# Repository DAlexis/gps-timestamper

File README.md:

GPS timestamper project
=======================

Open-source device based on STM32 that provides precision time stamps
of trigger signal connected to input. It use GPS PPS signal to provide
~1uS precision time mesurment. Also it makes self-calibration by PPS
every second.

Device may be used to synchronize any signals and data streams without
wired or wireless connection i.e. in geophysical researches, lightning 
detection networks, seismology and others

Currently project in protortype state and under development. Primary
function (precision timestamping) works correctly.

# Build
To build firmware you may have installed `arm-gcc` toolchain on your
linux system. If you do not need unit tests, simply comment out
corresponding line in root CMakeLists.txt (to build tests `gtest` should
be installed on your system)

Run `build.sh` and thats all. To flash MCU, connect ST-Link device to
PC and then run `flash.sh`.

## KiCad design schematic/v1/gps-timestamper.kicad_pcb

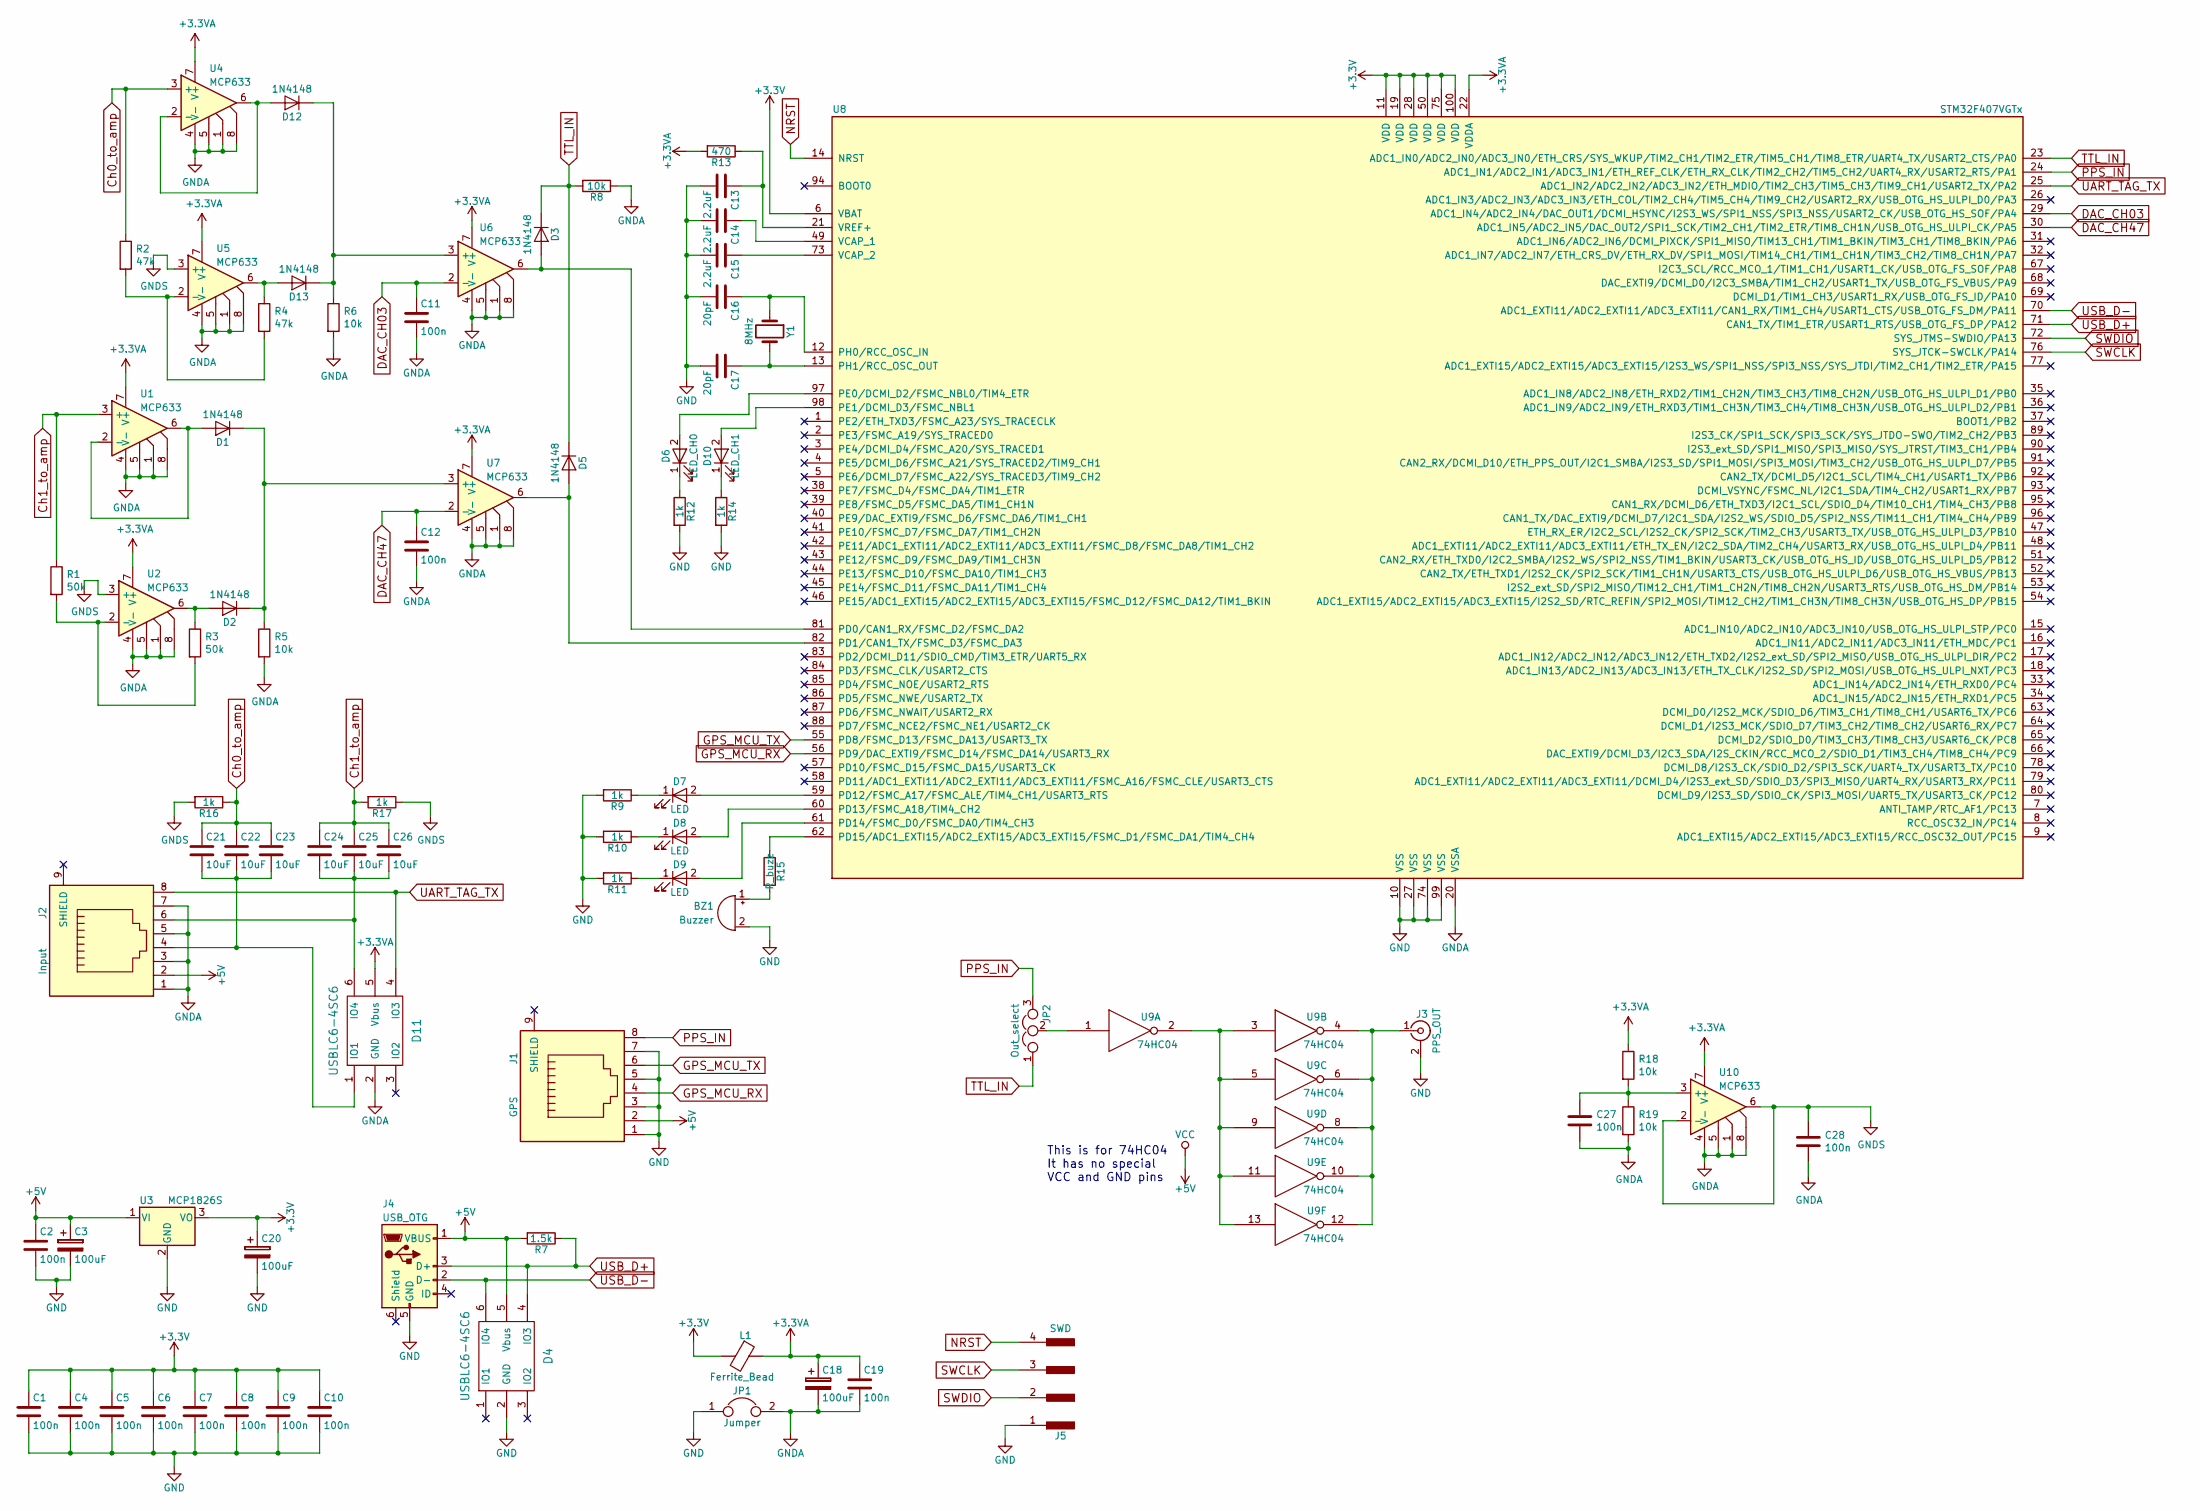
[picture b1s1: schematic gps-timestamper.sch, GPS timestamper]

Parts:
BZ1: Buzzer; Buzzer_12x9.5RM7.6
C1, C2, C4, C5, C6, C7, C8, C9, C10, C11, C12, C19, C27, C28: 100n; C_0805
C3, C18, C20: 100uF; CP_Tantalum_Case-B_EIA-3528-21_Wave
C13, C14, C15: 2.2uF; C_0805
C16, C17: 20pF; C_0805
C21, C22, C23, C24, C25, C26: 10uF; C_0805
D1, D2, D3, D5, D12, D13: 1N4148; D_SOD-323
D4, D11: USBLC6-4SC6; SOT-23-6
D6: LED_CH0; LED_0805
D7, D8, D9: LED; LED_0805
D10: LED_CH1; LED_0805
J1: GPS; RJ45_8
J2: Input; RJ45_8
J3: PPS_OUT; SMA_THT_Jack_Straight
J4: USB_OTG; USB_Micro-B
J5: SWD; Pin_Header_Straight_1x04_Pitch2.54mm
JP1: Jumper; GS2
JP2: Out_select; Pin_Header_Straight_1x03_Pitch2.54mm
L1: Ferrite_Bead; R_0805
R1, R3: 50k; R_0805
R2, R4: 47k; R_0805
R5, R6, R8, R18, R19: 10k; R_0805
R7: 1.5k; R_0805
R9, R10, R11, R12, R14, R16, R17: 1k; R_0805
R13: 470; R_0805
R15: R_buzz; R_0805
U1, U2, U4, U5, U6, U7, U10: MCP633; SOIC-8-N
U3: MCP1826S; SOT-223-3_TabPin2
U8: STM32F407VGTx; LQFP-100_14x14mm_Pitch0.5mm
U9: 74HC04; SOIC-14_N
Y1: 8MHz; Crystal_HC49-U_Vertical

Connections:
+3.3VA: C18.1, C19.1, D11.5 (Vbus), L1.1, R13.2, R18.1, U1.7 (V+), U2.7 (V+), U4.7 (V+), U5.7 (V+), U6.7 (V+), U7.7 (V+), U8.22 (VDDA), U10.7 (V+)
+3V3: C1.1, C4.1, C5.1, C6.1, C7.1, C8.1, C9.1, C10.1, C20.1, L1.2, U3.3 (VO), U8.6 (VBAT), U8.11 (VDD), U8.19 (VDD), U8.28 (VDD), U8.50 (VDD), U8.75 (VDD), U8.100 (VDD)
+5V: C2.1, C3.1, D4.5 (Vbus), J1.2, J2.2, J4.1 (VBUS), R7.2, U3.1 (VI), U9.14 (VCC)
Ch0_to_amp: C21.1, C22.1, C23.1, R2.1, R16.1, U4.3 (+)
Ch1_to_amp: C24.1, C25.1, C26.1, R1.1, R17.2, U1.3 (+)
DAC_CH03: C11.1, U6.2 (-), U8.29 (ADC1_IN4/ADC2_IN4/DAC_OUT1/DCMI_HSYNC/I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)
DAC_CH47: C12.1, U7.2 (-), U8.30 (ADC1_IN5/ADC2_IN5/DAC_OUT2/SPI1_SCK/TIM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)
GND: BZ1.2 (+), C1.2, C2.2, C3.2, C4.2, C5.2, C6.2, C7.2, C8.2, C9.2, C10.2, C13.2, C14.2, C15.2, C16.2, C17.2, C20.2, D4.2 (GND), J1.1, J1.3, J1.5, J1.7, J3.2 (Ext), J4.5 (GND), J5.1, JP1.1, R9.2, R10.2, R11.2, R12.2, R14.2, U3.2 (GND), U8.10 (VSS), U8.27 (VSS), U8.74 (VSS), U8.99 (VSS), U9.7 (GND)
GNDA: C11.2, C12.2, C18.2, C19.2, C27.2, C28.2, D11.2 (GND), J2.1, J2.3, J2.5, J2.7, JP1.2, R5.2, R6.2, R8.1, R19.2, U1.1, U1.4 (V-), U1.5, U1.8, U2.1, U2.4 (V-), U2.5, U2.8, U4.1, U4.4 (V-), U4.5, U4.8, U5.1, U5.4 (V-), U5.5, U5.8, U6.1, U6.4 (V-), U6.5, U6.8, U7.1, U7.4 (V-), U7.5, U7.8, U8.20 (VSSA), U10.1, U10.4 (V-), U10.5, U10.8
GNDS: C28.1, R16.2, R17.1, U2.3 (+), U5.3 (+), U10.2 (-), U10.6
GPS_MCU_RX: J1.4, U8.56 (PD9/DAC_EXTI9/FSMC_D14/FSMC_DA14/USART3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)
GPS_MCU_TX: J1.6, U8.55 (PD8/FSMC_D13/FSMC_DA13/USART3_TX)
NRST: J5.4, U8.14 (NRST)
unnamed: BZ1.1 (-), R15.2
unnamed: C13.1, R13.1, U8.21 (VREF+)
unnamed: C14.1, U8.49 (VCAP_1)
unnamed: C15.1, U8.73 (VCAP_2)
unnamed: C16.1, U8.12 (PH0/RCC_OSC_IN), Y1.1
unnamed: C17.1, U8.13 (PH1/RCC_OSC_OUT), Y1.2
unnamed: C21.2, C22.2, C23.2, D11.1 (IO1), J2.4
unnamed: C24.2, C25.2, C26.2, D11.6 (IO4), J2.6
unnamed: C27.1, R18.2, R19.1, U10.3 (+)
unnamed: D1.1 (K), D2.1 (K), R5.1, U7.3 (+)
unnamed: D1.2 (A), U1.2 (-), U1.6
unnamed: D2.2 (A), R3.1, U2.6
unnamed: D3.2 (A), U6.6, U8.81 (PD0/CAN1_RX/FSMC_D2/FSMC_DA2)
unnamed: D5.2 (A), U7.6, U8.82 (PD1/CAN1_TX/FSMC_D3/FSMC_DA3)
unnamed: D6.1 (K), R12.1
unnamed: D6.2 (A), U8.97 (PE0/DCMI_D2/FSMC_NBL0/TIM4_ETR)
unnamed: D7.1 (K), R9.1
unnamed: D7.2 (A), U8.59 (PD12/FSMC_A17/FSMC_ALE/TIM4_CH1/USART3_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)
unnamed: D8.1 (K), R10.1
unnamed: D8.2 (A), U8.60 (PD13/FSMC_A18/TIM4_CH2)
unnamed: D9.1 (K), R11.1
unnamed: D9.2 (A), U8.61 (PD14/FSMC_D0/FSMC_DA0/TIM4_CH3)
unnamed: D10.1 (K), R14.1
unnamed: D10.2 (A), U8.98 (PE1/DCMI_D3/FSMC_NBL1)
unnamed: D12.1 (K), D13.1 (K), R6.1, U6.3 (+)
unnamed: D12.2 (A), U4.2 (-), U4.6
unnamed: D13.2 (A), R4.1, U5.6
unnamed: J3.1 (In), U9.4, U9.6, U9.8, U9.10, U9.12
unnamed: JP2.2, U9.1
unnamed: R1.2, R3.2, U2.2 (-)
unnamed: R2.2, R4.2, U5.2 (-)
unnamed: R15.1, U8.62 (PD15/ADC1_EXTI15/ADC2_EXTI15/ADC3_EXTI1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)
unnamed: U9.2, U9.3, U9.5, U9.9, U9.11, U9.13
PPS_IN: J1.8, JP2.3, U8.24 (ADC1_IN1/ADC2_IN1/ADC3_IN1/ETH_REF_CLK/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)
SWCLK: J5.3, U8.76 (SYS_JTCK-SWCLK/PA14)
SWDIO: J5.2, U8.72 (SYS_JTMS-SWDIO/PA13)
TTL_IN: D3.1 (K), D5.1 (K), JP2.1, R8.2, U8.23 (ADC1_IN0/ADC2_IN0/ADC3_IN0/ETH_CRS/SYS_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)
UART_TAG_TX: D11.4 (IO3), J2.8, U8.25 (ADC1_IN2/ADC2_IN2/ADC3_IN2/ETH_MDIO/TIM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)
USB_D+: D4.4 (IO3), J4.3 (D+), R7.1, U8.71 (CAN1_TX/TIM1_ETR/USART1_RTS/USB_OTG_FS_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)
USB_D-: D4.6 (IO4), J4.2 (D-), U8.70 (ADC1_EXTI11/ADC2_EXTI11/ADC3_EXTI11/CAN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)

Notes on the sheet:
This is for 74HC04 It has no special VCC and GND pins

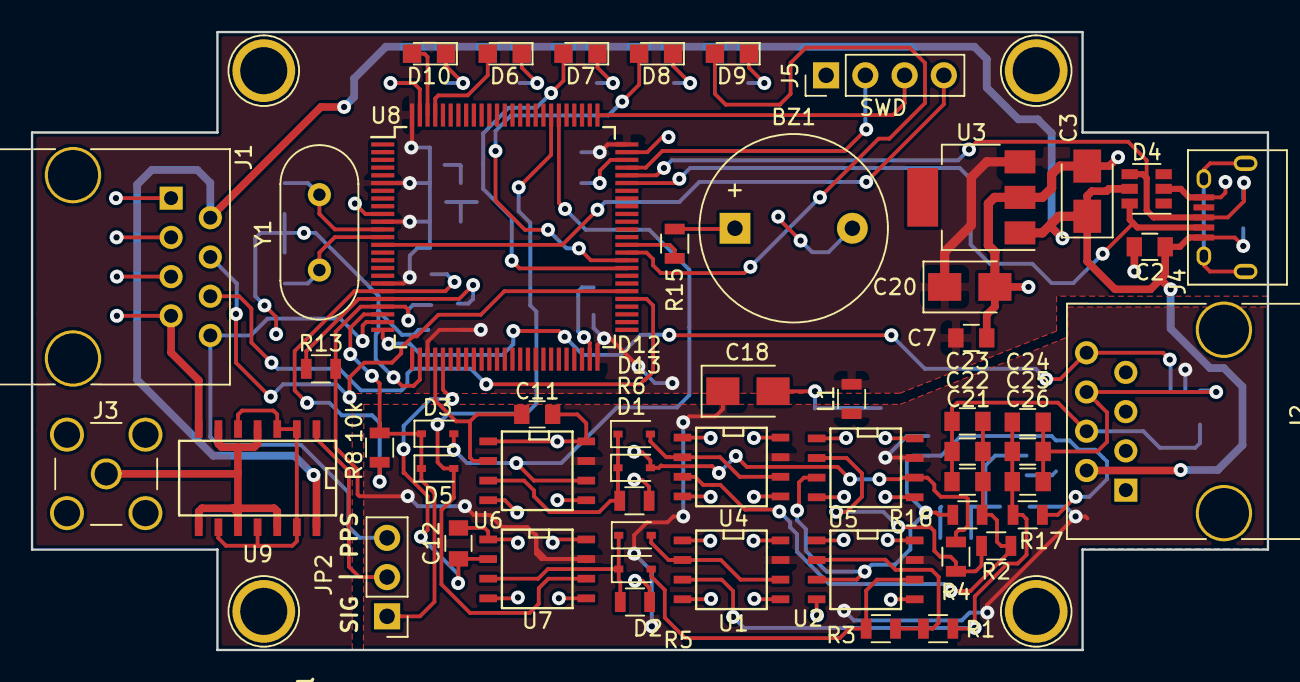
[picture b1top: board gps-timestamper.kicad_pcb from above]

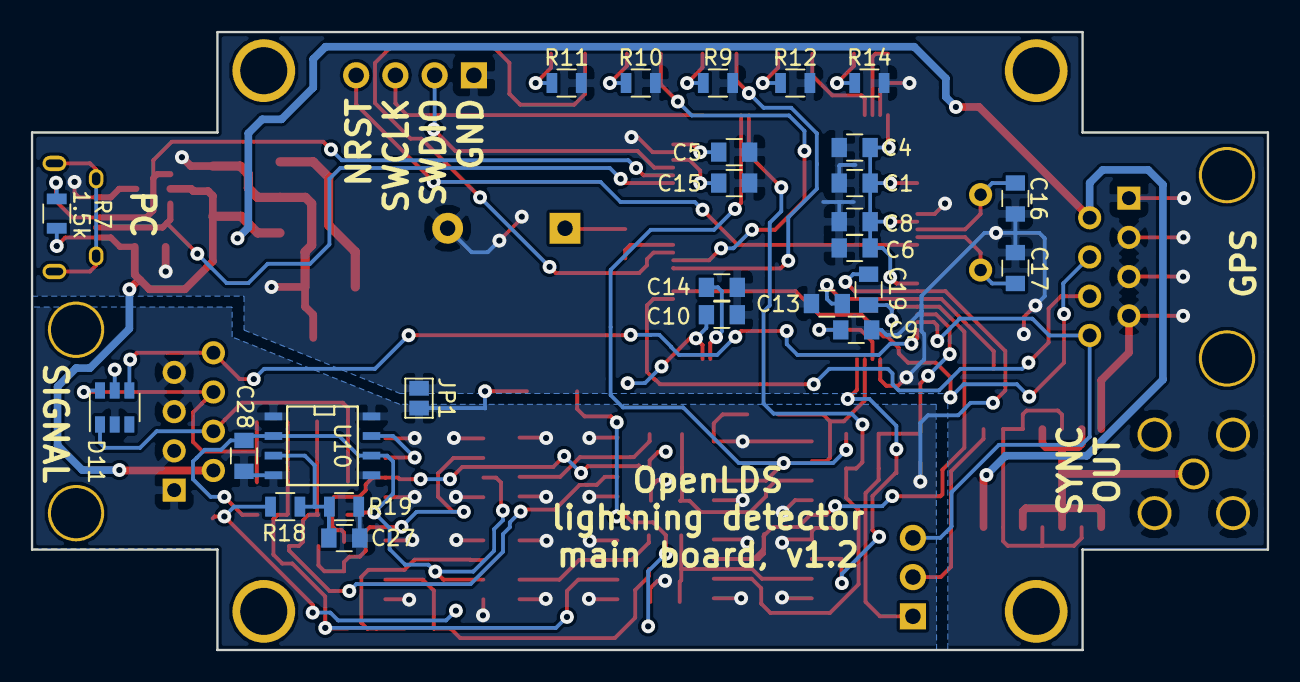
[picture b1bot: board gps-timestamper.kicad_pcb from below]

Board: 2 copper layers, 80.0 x 40.0 mm, 80 parts (26 on the bottom side), 53 nets.

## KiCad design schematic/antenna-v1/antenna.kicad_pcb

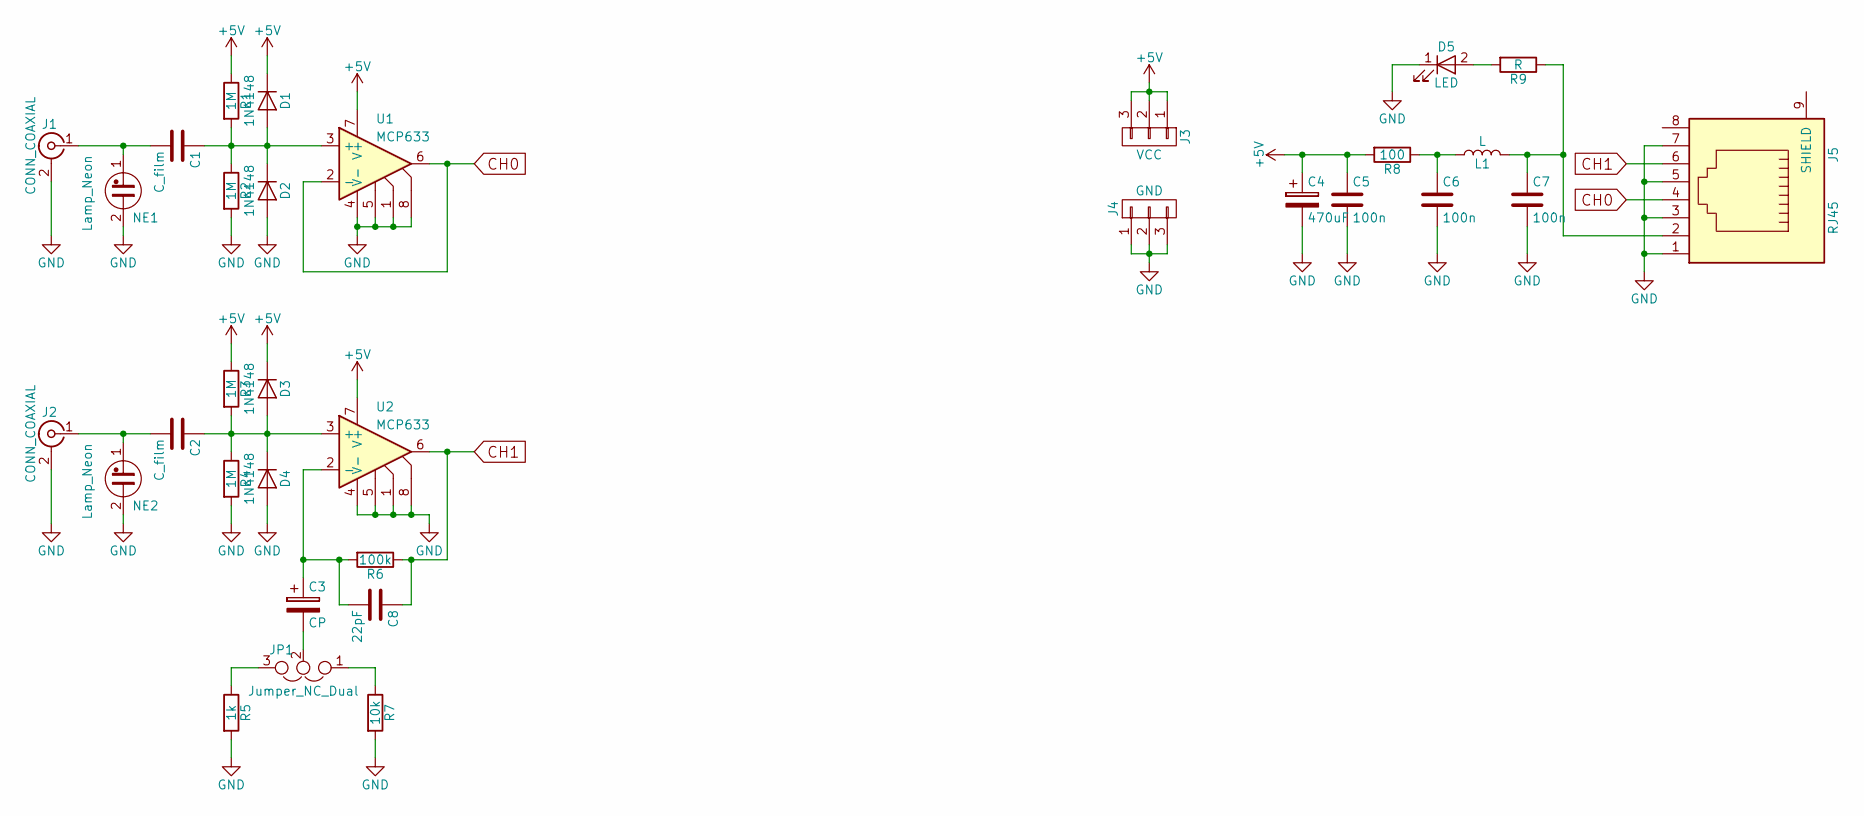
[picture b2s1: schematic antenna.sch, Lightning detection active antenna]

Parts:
C1, C2: C_film; C_Disc_D7.5mm_W5.0mm_P7.50mm
C3: CP; CP_Tantalum_Case-B_EIA-3528-21_Wave
C4: 470uF; CP_Tantalum_Case-D_EIA-7343-31_Wave
C5, C6, C7: 100n; C_0805
C8: 22pF; C_0805
D1, D2, D3, D4: 1N4148; D_SOD-323
D5: LED; LED_0805
J1, J2: CONN_COAXIAL; SMA_THT_Jack_Straight
J3: VCC; Pin_Header_Straight_1x03_Pitch2.54mm
J4: GND; Pin_Header_Straight_1x03_Pitch2.54mm
J5: RJ45; RJ45_8
JP1: Jumper_NC_Dual; Pin_Header_Straight_1x03_Pitch2.54mm
L1: L; R_0805
NE1, NE2: Lamp_Neon; C_Disc_D9.0mm_W5.0mm_P5.00mm
R1, R2, R3, R4: 1M; R_0805
R5: 1k; R_0805
R6: 100k; R_0805
R7: 10k; R_0805
R8: 100; R_0805
R9: R; R_0805
U1, U2: MCP633; SOIC-8_3.9x4.9mm_Pitch1.27mm

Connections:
+5V: C4.1, C5.1, D1.1 (K), D3.1 (K), J3.1, J3.2, J3.3, R1.1, R3.1, R8.2, U1.7 (V+), U2.7 (V+)
CH0: J5.4, U1.2 (-), U1.6
CH1: C8.1, J5.6, R6.1, U2.6
GND: C4.2, C5.2, C6.2, C7.2, D2.2 (A), D4.2 (A), D5.1 (K), J1.2 (Ext), J2.2 (Ext), J4.1, J4.2, J4.3, J5.1, J5.3, J5.5, J5.7, NE1.2, NE2.2, R2.2, R4.2, R5.2, R7.2, U1.1, U1.4 (V-), U1.5, U1.8, U2.1, U2.4 (V-), U2.5, U2.8
unnamed: C1.1, D1.2 (A), D2.1 (K), R1.2, R2.1, U1.3 (+)
unnamed: C1.2, J1.1 (In), NE1.1
unnamed: C2.1, D3.2 (A), D4.1 (K), R3.2, R4.1, U2.3 (+)
unnamed: C2.2, J2.1 (In), NE2.1
unnamed: C3.1, C8.2, R6.2, U2.2 (-)
unnamed: C3.2, JP1.2
unnamed: C6.1, L1.1, R8.1
unnamed: C7.1, J5.2, L1.2, R9.1
unnamed: D5.2 (A), R9.2
unnamed: JP1.1, R7.1
unnamed: JP1.3, R5.1

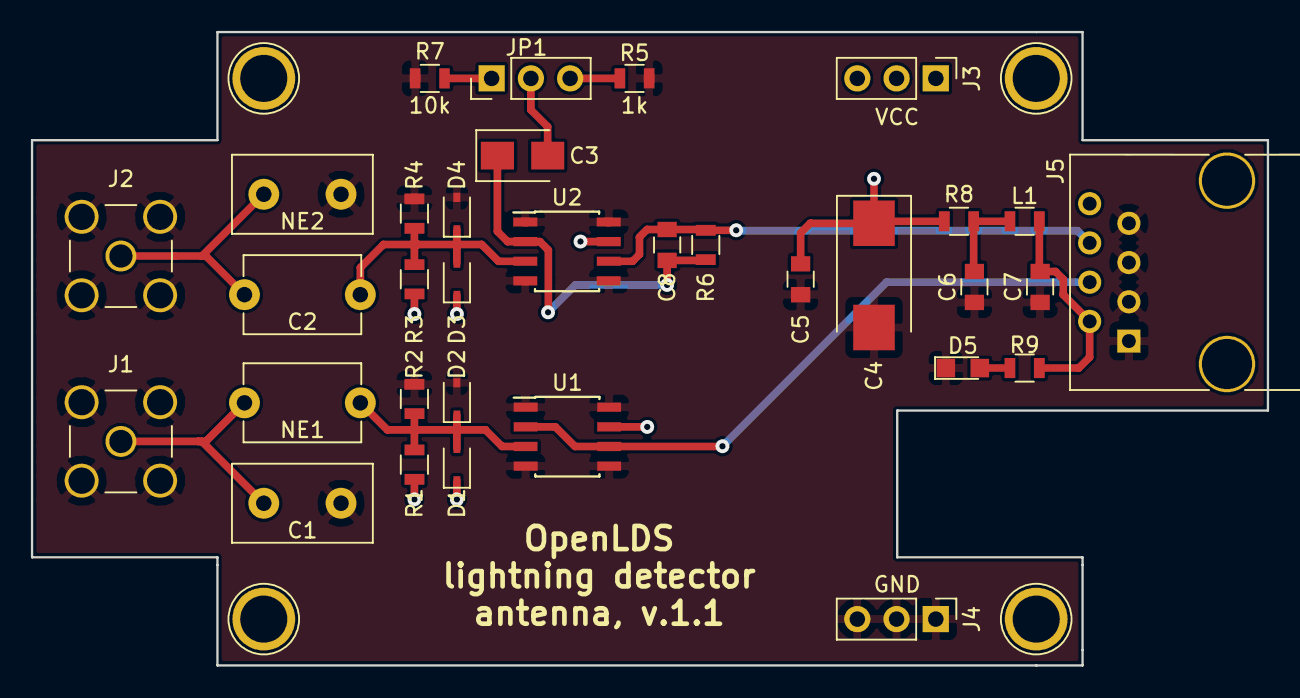
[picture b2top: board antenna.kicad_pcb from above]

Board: 2 copper layers, 80.0 x 41.0 mm, 33 parts (0 on the bottom side), 15 nets.

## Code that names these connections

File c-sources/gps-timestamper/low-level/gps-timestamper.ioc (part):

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Mcu.Name=STM32F407V(E-G)Tx
Mcu.Package=LQFP100
Mcu.UserName=STM32F407VGTx
PA0-WKUP.GPIOParameters=GPIO_ModeDefaultPP,GPIO_PuPd,GPIO_Label
PA0-WKUP.GPIO_Label=Signal
PA0-WKUP.GPIO_ModeDefaultPP=GPIO_MODE_AF_PP
PA0-WKUP.GPIO_PuPd=GPIO_PULLDOWN
PA0-WKUP.Signal=S_TIM2_CH1_ETR
PA1.GPIOParameters=GPIO_ModeDefaultPP,GPIO_PuPd,GPIO_Label
PA1.GPIO_Label=PPS
PA1.GPIO_ModeDefaultPP=GPIO_MODE_AF_PP
PA1.GPIO_PuPd=GPIO_PULLUP
PA1.Signal=S_TIM2_CH2
PA10.GPIOParameters=GPIO_Label
PA10.GPIO_Label=JSON_OUTPUT_USART1_RX
PA10.Mode=Asynchronous
PA10.Signal=USART1_RX
PA11.Mode=Device_Only
PA11.Signal=USB_OTG_FS_DM
PA12.Mode=Device_Only
PA12.Signal=USB_OTG_FS_DP
PA13.Mode=Serial_Wire
PA13.Signal=SYS_JTMS-SWDIO
PA14.Mode=Serial_Wire
PA14.Signal=SYS_JTCK-SWCLK
PA2.GPIOParameters=GPIO_Label
PA2.GPIO_Label=TAG_USART2_TX
PA2.Mode=Asynchronous
PA2.Signal=USART2_TX
PA3.GPIOParameters=GPIO_Label
PA3.GPIO_Label=TAG_USART2_RX
PA3.Mode=Asynchronous
PA3.Signal=USART2_RX
PA4.GPIOParameters=GPIO_Label
PA4.GPIO_Label=DAC_treshold_03
PA4.Signal=COMP_DAC1_group
PA5.GPIOParameters=GPIO_Label
PA5.GPIO_Label=DAC_treshold_47
PA5.Signal=COMP_DAC2_group
PA9.GPIOParameters=GPIO_Label
PA9.GPIO_Label=JSON_OUTPUT_USART1_TX
PA9.Mode=Asynchronous
PA9.Signal=USART1_TX
PD0.GPIOParameters=GPIO_Label
PD0.GPIO_Label=Sig_ch0
PD0.Signal=GPIO_Input
PD1.GPIOParameters=GPIO_Label
PD1.GPIO_Label=Sig_ch1
PD1.Signal=GPIO_Input
PD12.GPIOParameters=GPIO_Label
PD12.GPIO_Label=LED_2
PD12.Signal=GPIO_Output
PD13.GPIOParameters=GPIO_Label
PD13.GPIO_Label=LED_3
PD13.Signal=GPIO_Output
PD14.GPIOParameters=GPIO_Label
PD14.GPIO_Label=LED_4
PD14.Signal=GPIO_Output
PD15.GPIOParameters=GPIO_Label
PD15.GPIO_Label=Sound_pin
PD15.Signal=GPIO_Output
PD2.GPIOParameters=GPIO_Label
PD2.GPIO_Label=Sig_ch2
PD2.Signal=GPIO_Input
PD3.GPIOParameters=GPIO_Label
PD3.GPIO_Label=SIg_ch3
PD3.Signal=GPIO_Input
PD4.GPIOParameters=GPIO_Label
PD4.GPIO_Label=Sig_ch4
PD4.Signal=GPIO_Input
PD5.GPIOParameters=GPIO_Label
PD5.GPIO_Label=Sig_ch5
PD5.Signal=GPIO_Input
PD6.GPIOParameters=GPIO_Label
PD6.GPIO_Label=Sig_ch6
PD6.Signal=GPIO_Input
PD7.GPIOParameters=GPIO_Label
PD7.GPIO_Label=Sig_ch7
PD7.Signal=GPIO_Input
PD8.Mode=Asynchronous
PD8.Signal=USART3_TX
PD9.Mode=Asynchronous
PD9.Signal=USART3_RX
PE0.GPIOParameters=GPIO_Label
PE0.GPIO_Label=LED_0
PE0.Signal=GPIO_Output
PE1.GPIOParameters=GPIO_Label
PE1.GPIO_Label=LED_1
PE1.Signal=GPIO_Output
PE7.GPIOParameters=GPIO_Label
PE7.GPIO_Label=LED_ch7
PE7.Signal=GPIO_Output
PH0-OSC_IN.Mode=HSE-External-Oscillator
PH0-OSC_IN.Signal=RCC_OSC_IN
PH1-OSC_OUT.Mode=HSE-External-Oscillator
PH1-OSC_OUT.Signal=RCC_OSC_OUT
RCC.HSE_VALUE=8000000
RCC.SYSCLKFreq_VALUE=96000000
RCC.SYSCLKSource=RCC_SYSCLKSOURCE_PLLCLK
board=gps-timestamper

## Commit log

2016-11-30 [firmware] Led blink stub. Builds with CMake, not tested
2016-12-01 [firmware] Led blinks works
2016-12-01 [firmware] USB CDC works
2016-12-05 [firmware] stupid port reading works
2016-12-05 [firmware] FreeRTOS support added successfuly
2016-12-06 [firmware] NMEA receiver and parser added; unit test on PC added; directories structure improved; USB debug messages delay added (to prevent losed messages)
2016-12-07 [firmware] Low-level capture works. Some high-level capture code written but not tested
2016-12-09 [firmware] Device protorype works. Invalid round time when gps misses GPGPA over uart
2017-04-05 Schematic and doc initial
2017-04-12 Fixed timestamps seems working
2017-04-13 Fixes: queue use correct size(), queue overflow message, all messages changed to JSON format
2017-04-13 Readmo updated
2017-04-13 Updated stm32 copyrights in generated files
2017-04-13 [PCB] [firmware] Schematics added, GPIO labels added, DAC generated code added
2017-04-18 [PCB] [firmware] PCB: version 1 schematic seems normal, firmware: last second period output added
2017-04-19 [PCB] pcb seems done, silkscreen sims accurate
2017-04-20 [PCB] Design improved. RJ-45 input, buffered PPS output
2017-04-25 [PCB] Active antenna schmatics
2017-04-28 [PCB] Antenna done and input trigger output added for main device
2018-01-12 Fix for PCBs: op amps
2018-02-14 v1.1 PCB group done
2018-11-22 GTest external dependency removed, main module schematic upgraded to latest kicad version
2018-12-15 STM firmware update
2019-03-19 New fixed schematics
2019-03-27 Threshold voltage controller, leds, some refactoring
